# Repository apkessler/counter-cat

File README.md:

counter-cat
===========

Andrew Kessler, 2013

A mechatronic solution to keeping cats off of kitchen counters (and other places they shouldn't be).

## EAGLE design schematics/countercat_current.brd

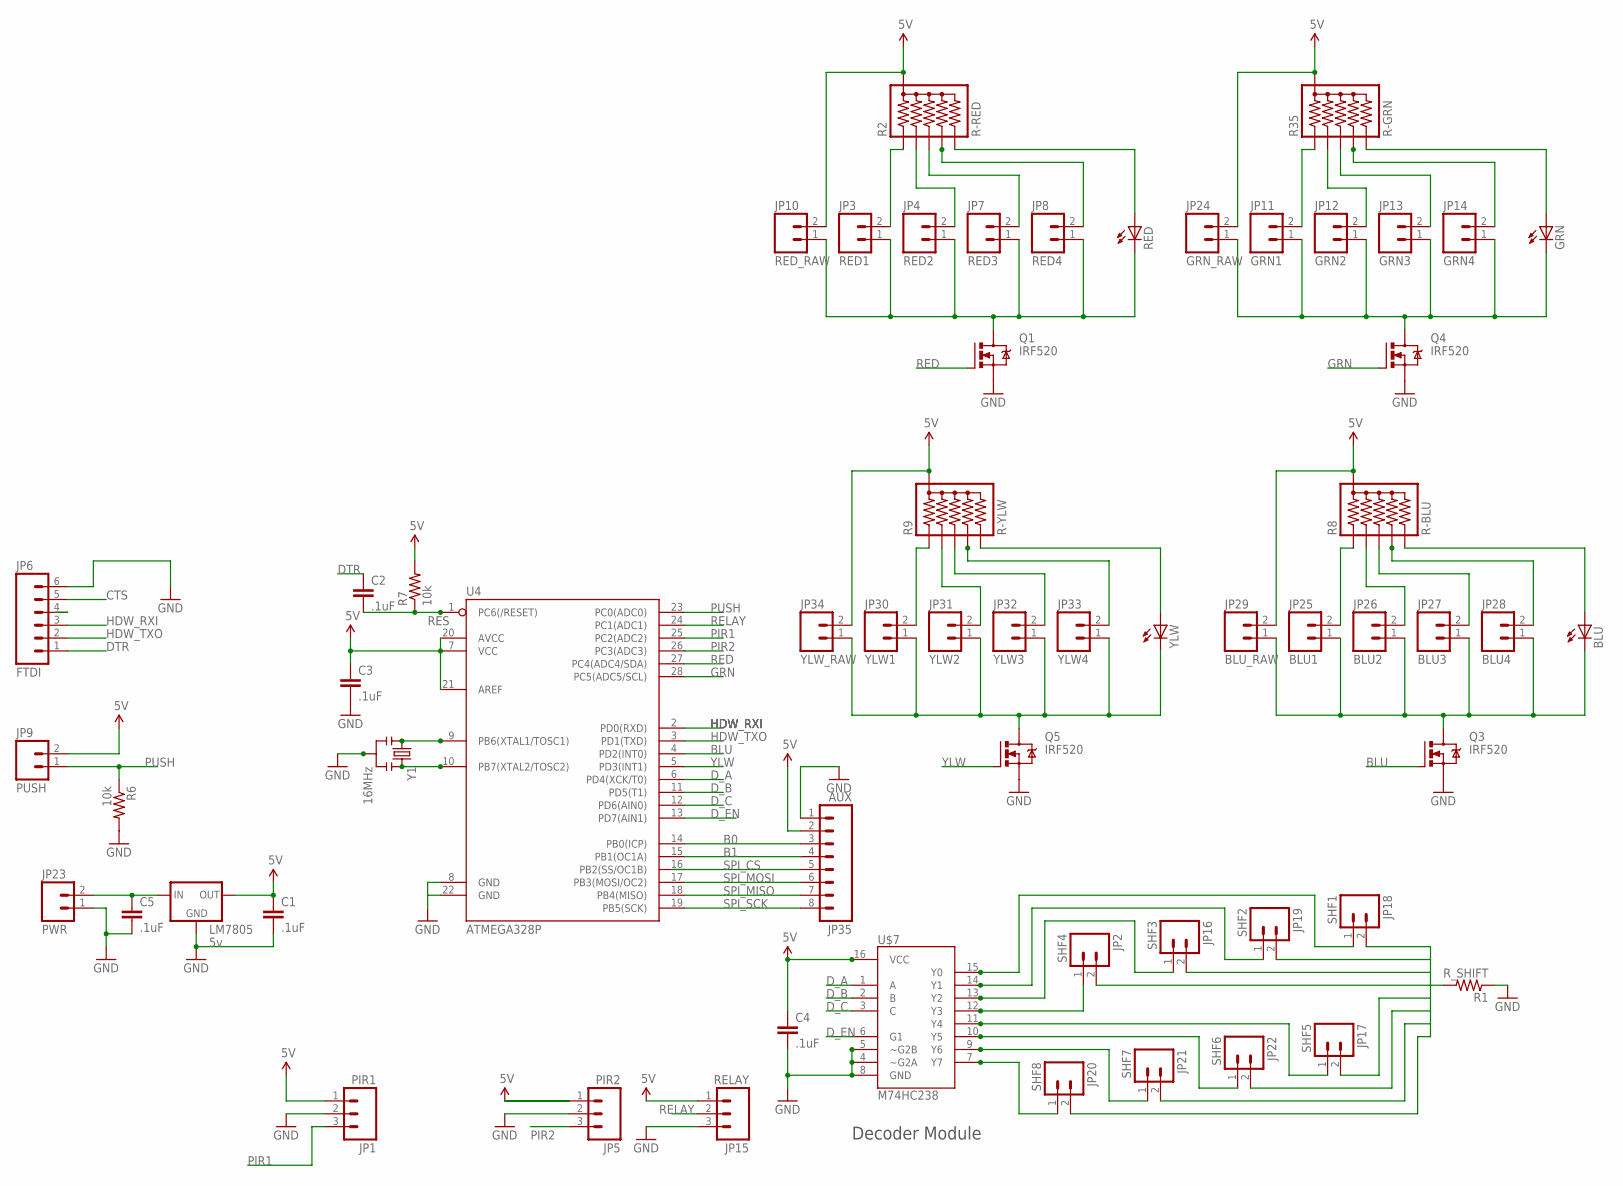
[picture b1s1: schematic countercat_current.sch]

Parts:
BLU: LED3MM
C1, C2, C3, C4, C5: .1uF; CAP-PTH-SMALL2
GRN: LED3MM
JP1: PIR1; MOLEX-1X3
JP2: SHF4; MOLEX-1X2
JP3: RED1; MOLEX-1X2
JP4: RED2; MOLEX-1X2
JP5: PIR2; MOLEX-1X3
JP6: FTDI; 1X06_LOCK
JP7: RED3; MOLEX-1X2
JP8: RED4; MOLEX-1X2
JP9: PUSH; MOLEX-1X2
JP10: RED_RAW; MOLEX-1X2
JP11: GRN1; MOLEX-1X2
JP12: GRN2; MOLEX-1X2
JP13: GRN3; MOLEX-1X2
JP14: GRN4; MOLEX-1X2
JP15: RELAY; MOLEX-1X3
JP16: SHF3; MOLEX-1X2
JP17: SHF5; MOLEX-1X2
JP18: SHF1; MOLEX-1X2
JP19: SHF2; MOLEX-1X2
JP20: SHF8; MOLEX-1X2
JP21: SHF7; MOLEX-1X2
JP22: SHF6; MOLEX-1X2
JP23: PWR; MOLEX-1X2
JP24: GRN_RAW; MOLEX-1X2
JP25: BLU1; MOLEX-1X2
JP26: BLU2; MOLEX-1X2
JP27: BLU3; MOLEX-1X2
JP28: BLU4; MOLEX-1X2
JP29: BLU_RAW; MOLEX-1X2
JP30: YLW1; MOLEX-1X2
JP31: YLW2; MOLEX-1X2
JP32: YLW3; MOLEX-1X2
JP33: YLW4; MOLEX-1X2
JP34: YLW_RAW; MOLEX-1X2
JP35: AUX; 1X08_LOCK
LM7805: 5v; TO220-IGO
Q1, Q3, Q4, Q5: IRF520; TO220BV
R1: R_SHIFT; AXIAL-0.4
R2: R-RED; RPACK-SIP-PTH-5
R6, R7: 10k; AXIAL-0.4
R8: R-BLU; RPACK-SIP-PTH-5
R9: R-YLW; RPACK-SIP-PTH-5
R35: R-GRN; RPACK-SIP-PTH-5
RED: LED3MM
U4: ATMEGA328P; DIL28-3
U$7: M74HC238; DIL16
Y1: 16MHz; RESONATOR-PTH
YLW: LED3MM

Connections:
5V: C1.1, C3.1, C4.1, JP1.1, JP5.1, JP9.2, JP10.2, JP15.1, JP24.2, JP29.2, JP34.2, JP35.2, LM7805.OUT, R2.P$1 (1), R7.P$2 (2), R8.P$1 (1), R9.P$1 (1), R35.P$1 (1), U4.7 (VCC), U4.20 (AVCC), U4.21 (AREF), U$7.16 (VCC)
B0: JP35.3, U4.14 (PB0(ICP))
B1: JP35.4, U4.15 (PB1(OC1A))
BLU: Q3.G, U4.4 (PD2(INT0))
CTS: JP6.5
DTR: C2.1, JP6.1
D_A: U4.6 (PD4(XCK/T0)), U$7.1 (A)
D_B: U4.11 (PD5(T1)), U$7.2 (B)
D_C: U4.12 (PD6(AIN0)), U$7.3 (C)
D_EN: U4.13 (PD7(AIN1)), U$7.6 (G1)
GND: C1.2, C3.2, C4.2, C5.2, JP1.2, JP5.2, JP6.6, JP15.3, JP23.1, JP35.1, LM7805.GND, Q1.S, Q3.S, Q4.S, Q5.S, R1.P$1 (1), R6.P$2 (2), U4.8 (GND), U4.22 (GND), U$7.4 (~G2A), U$7.5 (~G2B), U$7.8 (GND), Y1.2
GRN: Q4.G, U4.28 (PC5(ADC5/SCL))
HDW_RXI: JP6.3, U4.2 (PD0(RXD))
HDW_TXO: JP6.2, U4.3 (PD1(TXD))
unnamed: JP17.1, U$7.11 (Y4)
unnamed: JP3.1, JP4.1, JP7.1, JP8.1, JP10.1, Q1.D, RED.K (C)
unnamed: U4.9 (PB6(XTAL1/TOSC1)), Y1.1
unnamed: GRN.K (C), JP11.1, JP12.1, JP13.1, JP14.1, JP24.1, Q4.D
unnamed: JP11.2, R35.P$2 (2)
unnamed: U4.10 (PB7(XTAL2/TOSC2)), Y1.3
unnamed: JP4.2, R2.P$3 (3)
unnamed: JP12.2, R35.P$3 (3)
unnamed: JP13.2, R35.P$4 (4)
unnamed: JP14.2, R35.P$5 (5)
unnamed: JP7.2, R2.P$4 (4)
unnamed: JP8.2, R2.P$5 (5)
unnamed: R2.P$6 (6), RED.A
unnamed: JP3.2, R2.P$2 (2)
unnamed: JP2.2, JP16.2, JP17.2, JP18.2, JP19.2, JP20.2, JP21.2, JP22.2, R1.P$2 (2)
unnamed: JP18.1, U$7.15 (Y0)
unnamed: JP19.1, U$7.14 (Y1)
unnamed: JP16.1, U$7.13 (Y2)
unnamed: JP2.1, U$7.12 (Y3)
unnamed: JP21.1, U$7.9 (Y6)
unnamed: JP22.1, U$7.10 (Y5)
unnamed: JP20.1, U$7.7 (Y7)
unnamed: BLU.K (C), JP25.1, JP26.1, JP27.1, JP28.1, JP29.1, Q3.D
unnamed: JP26.2, R8.P$3 (3)
unnamed: JP27.2, R8.P$4 (4)
unnamed: JP28.2, R8.P$5 (5)
unnamed: BLU.A, R8.P$6 (6)
unnamed: JP25.2, R8.P$2 (2)
unnamed: JP30.1, JP31.1, JP32.1, JP33.1, JP34.1, Q5.D, YLW.K (C)
unnamed: JP31.2, R9.P$3 (3)
unnamed: JP32.2, R9.P$4 (4)
unnamed: JP33.2, R9.P$5 (5)
unnamed: R9.P$6 (6), YLW.A
unnamed: GRN.A, R35.P$6 (6)
unnamed: JP30.2, R9.P$2 (2)
PIR1: JP1.3, U4.25 (PC2(ADC2))
PIR2: JP5.3, U4.26 (PC3(ADC3))
PUSH: JP9.1, R6.P$1 (1), U4.23 (PC0(ADC0))
RED: Q1.G, U4.27 (PC4(ADC4/SDA))
RELAY: JP15.2, U4.24 (PC1(ADC1))
RES: C2.2, R7.P$1 (1), U4.1 (PC6(/RESET))
SPI_CS: JP35.5, U4.16 (PB2(SS/OC1B))
SPI_MISO: JP35.7, U4.18 (PB4(MISO))
SPI_MOSI: JP35.6, U4.17 (PB3(MOSI/OC2))
SPI_SCK: JP35.8, U4.19 (PB5(SCK))
VB: C5.1, JP23.2, LM7805.IN
YLW: Q5.G, U4.5 (PD3(INT1))

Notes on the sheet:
Decoder Module

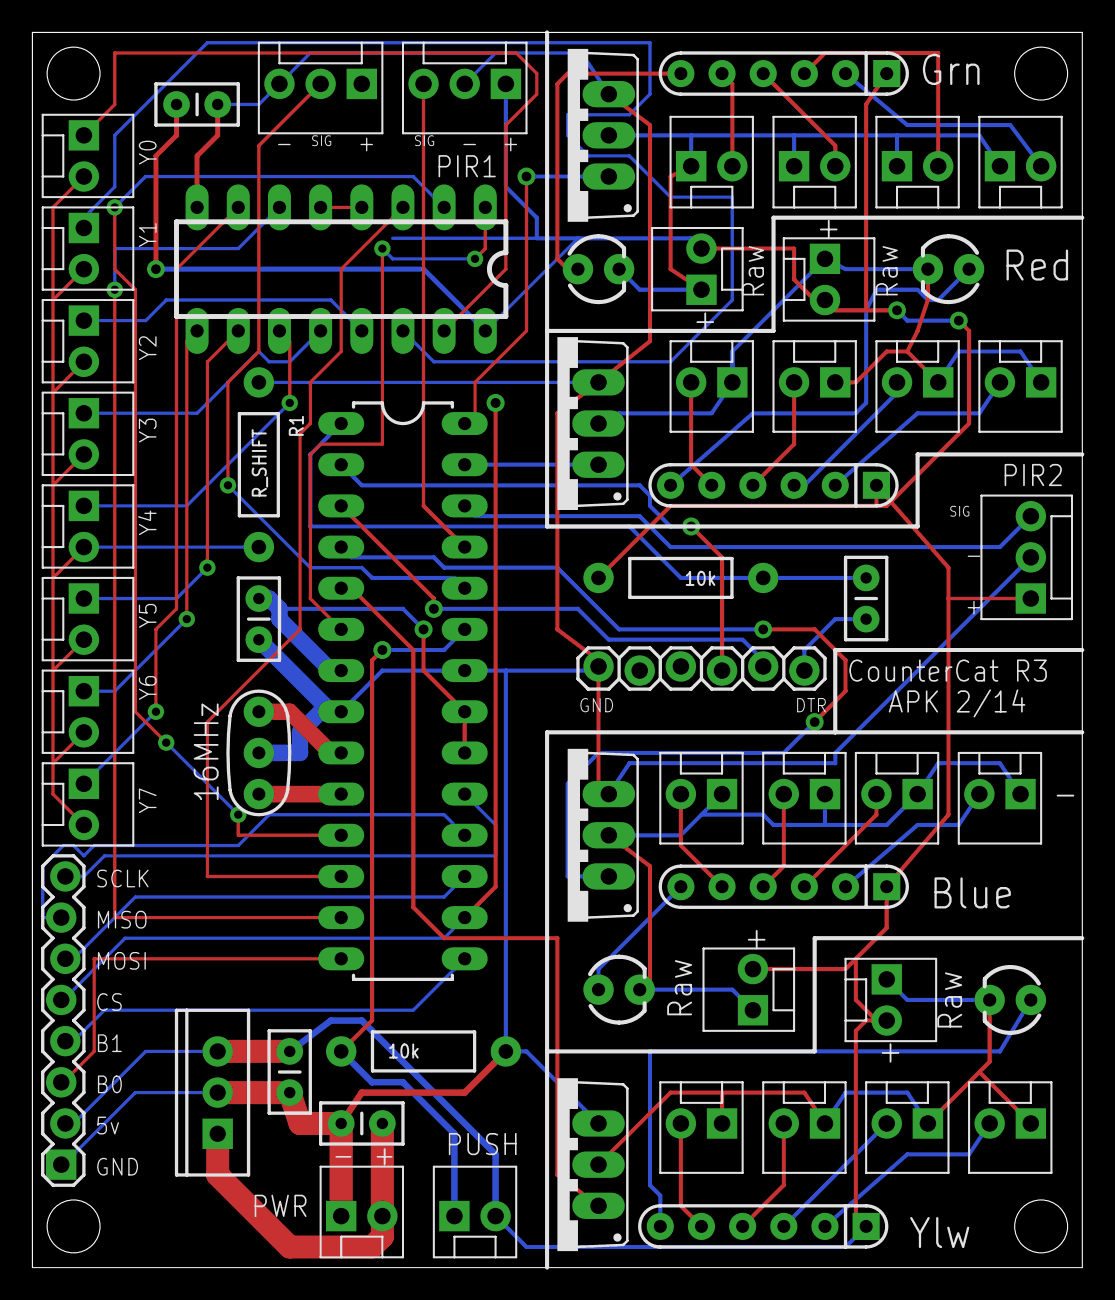
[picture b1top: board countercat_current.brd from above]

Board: 2 copper layers, 64.8 x 76.2 mm, 59 parts (0 on the bottom side), 60 nets.

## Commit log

2013-08-25 Added to README.
2013-08-28 Added basic opencv example with sample image.
2013-08-29 Added arduino file to turn on blender based on PIR
2013-08-29 Added comments and tested.
2013-08-31 Added button and green/red led code, pause state
2013-09-01 Added fritzing file
2013-09-01 Added button debouce
2013-09-02 Fixed potential bug where alarm could go off immediately after unpausing, comment changes
2013-11-13 Remapped pins to conform to PCB. Added DIP switches as inputs.
2014-01-01 Added Eagle schematic, removed fritzing file
2014-01-01 Slight change.
2014-01-03 Moved schematic and arduino code out of arduino folder
2014-01-03 Added SolidWorks parts.
2014-01-05 Moved code into subfolder; added sample camera module code
2014-01-06 Changed some colors, added relay control PCB, uno
2014-01-06 Added camera CAD model
2014-01-07 Got rid of unused parts.
2014-01-07 Made box sqaure!
2014-01-07 Mounted countercat PCB
2014-01-07 Deleted LED model
2014-01-07 Moved power input/output to left side. Got rid of external LEDs
2014-01-07 Made box bigger again
2014-01-07 Added more nuts
2014-01-07 Added text, moved switch and power adapter
2014-01-07 Got rid of switch hole on back plate
2014-01-08 Added fuse holder, radio shack pcb, made power switch hole bigger
2014-01-08 Rotated view
2014-01-09 Added laser cutting files (SolidWorks drawing, and Illustrator paths.)
2014-01-10 Changed top plate to have emoticons instead of text
2014-01-14 Changed top plate to overhand on all sides
2014-01-14 Changed the LED hookup schematic
2014-01-15 Made outlet holes bigger
2014-01-18 Added support for safey sensor trigger
2014-01-18 Added options for not using PIR2
2014-01-18 Started board design
2014-01-21 Rev3. Made whole box smaller, thinner. Added new LED mounts for top.
2014-01-22 Added dc_jack, changed size of 550 recpt to match reality, added button/switch holes
2014-01-22 Changed board size, add shifter
2014-01-23 Updated board and schematic
2014-01-24 Autorouted and adjusted results
2014-01-24 Added PCB to assembly
2014-01-24 Changed eye shape
2014-01-28 Autorouted and DRC'd
2014-01-28 Got rid of relay on board. Made smaller, swapepd out shift reg. for decoder
2014-01-28 Added Gerber files.
2014-01-29 Made rev3 pcb smaller and added relay pcb back in
2014-01-29 Fixed error with shorted DTR net in schematic
2014-02-07 Implemented scanning eye, added more LED colors. Updated to Rev3 board
2014-02-07 Archived Eagle files correspond to physical Rev3 board.
2014-02-07 Updated current schematic file to fix mistakes from Rev3 board.
2014-02-07 Added PDF of board schematic
2014-02-09 Changed too counter vs millis() for timing things.
2014-02-09 Made adjustments to fix timer rates, added more debouncing

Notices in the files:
parts and their libraries:
SparkFun-Resistors: Licensing: CC v3.0 Share-Alike You are welcome to use this library for commercial purposes.
